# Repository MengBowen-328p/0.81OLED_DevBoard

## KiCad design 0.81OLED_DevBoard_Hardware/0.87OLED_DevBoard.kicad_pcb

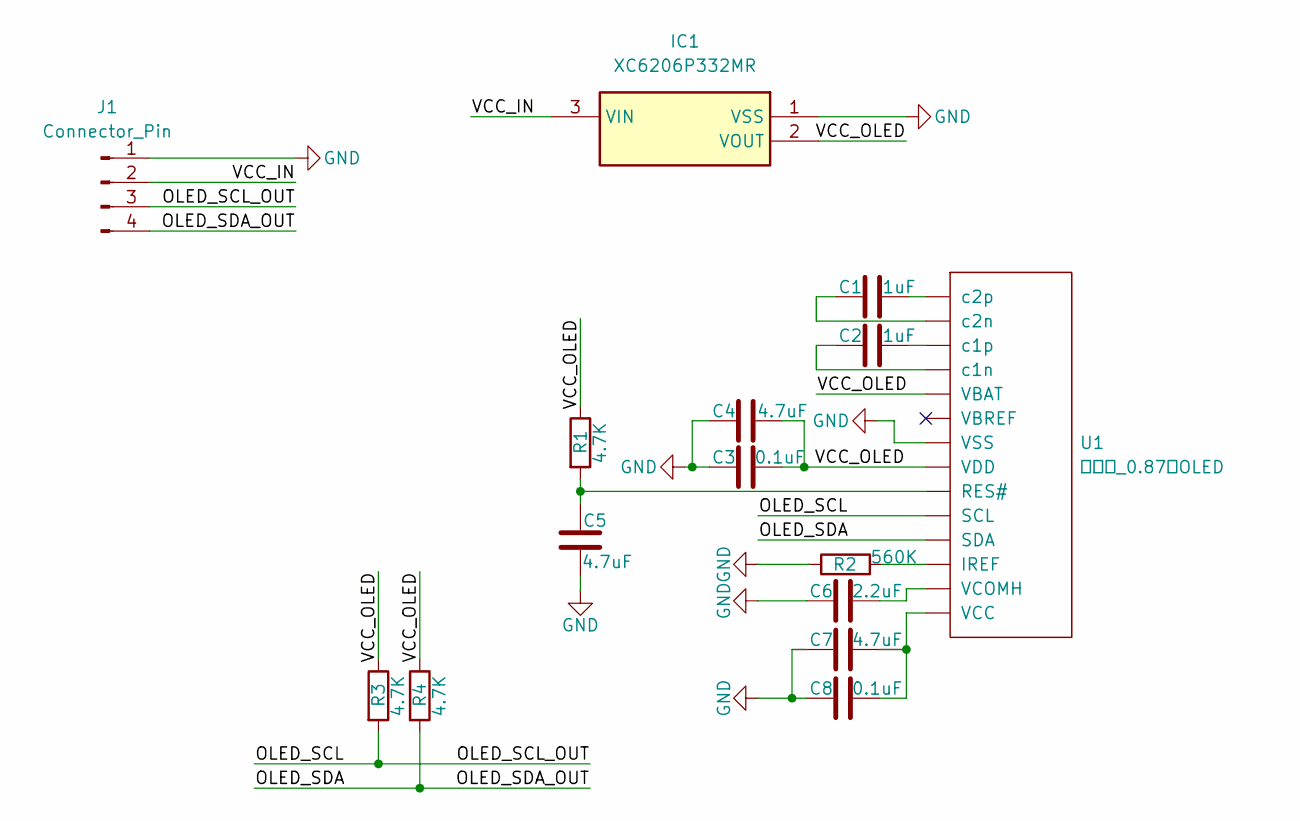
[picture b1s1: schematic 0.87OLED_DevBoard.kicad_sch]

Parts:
C1, C2: 1uF; C_0603_1608Metric
C3, C8: 0.1uF; C_0603_1608Metric
C4, C5, C7: 4.7uF; C_0603_1608Metric
C6: 2.2uF; C_0603_1608Metric
IC1: XC6206P332MR; SOT95P240X115-3N; Manufacturer_Part_Number XC6206P332MR
J1: Connector_Pin; PinHeader_1x04_P2.54mm_Vertical
R1, R3, R4: 4.7K; R_0603_1608Metric
R2: 560K; R_0603_1608Metric
U1: 中景园_0.87寸OLED; 中景园0.87寸OLED

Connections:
/OLED_SCL: J1.3, R3.2, U1.10 (SCL)
/OLED_SDA: J1.4, R4.2, U1.11 (SDA)
/VCC_IN: IC1.3 (VIN), J1.2
/VCC_OLED: C3.2, C4.2, IC1.2 (VOUT), R1.1, R3.1, R4.1, U1.5 (VBAT), U1.8 (VDD)
GND: C3.1, C4.1, C5.1, C6.1, C7.1, C8.1, IC1.1 (VSS), J1.1, R2.1, U1.7 (VSS)
unnamed: R2.2, U1.12 (IREF)
unnamed: C5.2, R1.2, U1.9 (RES#)
unnamed: C7.2, C8.2, U1.14 (VCC)
unnamed: C6.2, U1.13 (VCOMH)
unnamed: C2.1, U1.4 (c1n)
unnamed: C2.2, U1.3 (c1p)
unnamed: C1.1, U1.2 (c2n)
unnamed: C1.2, U1.1 (c2p)

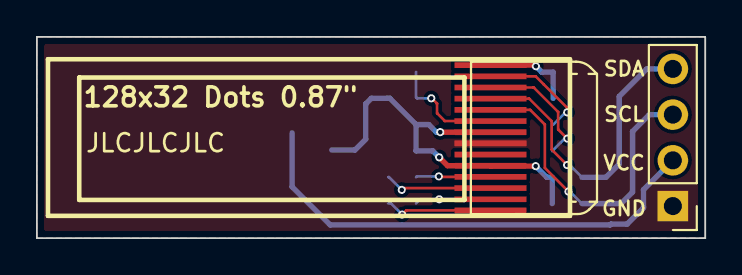
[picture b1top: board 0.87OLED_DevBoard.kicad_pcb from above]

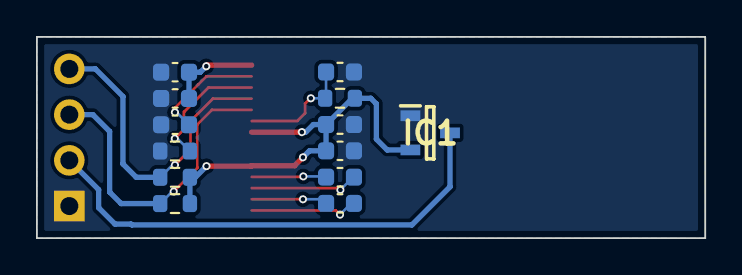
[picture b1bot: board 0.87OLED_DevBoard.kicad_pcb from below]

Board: 2 copper layers, 37.1 x 11.2 mm, 15 parts (13 on the bottom side), 13 nets.

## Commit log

2023-11-24 Finished HardWare
2023-11-27 Finish PCB Layout
2023-12-05 Update Firmware
